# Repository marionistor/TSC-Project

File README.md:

# OpenBook

OpenBook este un e-book reader open-source, construit pentru consum mic de energie și versatilitate. Folosește microcontrollerul ESP32-C6-WROOM-1-N8, un ecran e-paper, senzori ambientali, ceas în timp real și stocare extinsă, alimentate de o baterie reîncărcabilă.

## Bill of Materials

| Componentă | Descriere | Link Achiziție | Documentație |
|------------|-----------|----------------|--------------|
| ESP32-C6-WROOM-1-N8 | Microcontroler cu Wi-Fi 6, BLE 5.0 | [Mouser](https://ro.mouser.com/ProductDetail/Espressif-Systems/ESP32-C6-WROOM-1-N8) | [Datasheet](https://www.espressif.com/sites/default/files/documentation/esp32-c6-wroom-1_wroom-1u_datasheet_en.pdf) |
| BME680 | Senzor temperatură, umiditate, presiune, VOC | [Mouser](https://ro.mouser.com/ProductDetail/Bosch-Sensortec/BME680) | [Datasheet](https://www.bosch-sensortec.com/media/boschsensortec/downloads/datasheets/bst-bme680-ds001.pdf) |
| DS3231SN | Ceas în timp real | [Mouser](https://ro.mouser.com/ProductDetail/Analog-Devices/DS3231SN) | [Datasheet](https://www.analog.com/media/en/technical-documentation/data-sheets/DS3231.pdf) |
| W25Q512JVEIQ | Memorie Flash 64MB | [Mouser](https://ro.mouser.com/ProductDetail/Winbond/W25Q512JVEIQ) | [Datasheet](https://www.winbond.com/resource-files/W25Q512JV%20SPI%20RevB%2006252019%20KMS.pdf) |
| MicroSD Slot (112A-TAAR-R03) | Slot card microSD | [Mouser](https://ro.mouser.com/ProductDetail/Attend/112A-TAAR-R03) | [Datasheet](https://www.attend.com.tw/data/download/file/112A-TAAR-R03_Spec.pdf) |
| MCP73831T-5ACI/OT | Încărcător baterie | [Mouser](https://ro.mouser.com/ProductDetail/Microchip-Technology/MCP73831T-5ACI-OT) | [Datasheet](https://ww1.microchip.com/downloads/en/DeviceDoc/MCP73831-Family-Data-Sheet-DS20001984H.pdf) |
| MAX17048G+T10 | Indicator nivel baterie | [Mouser](https://ro.mouser.com/ProductDetail/Analog-Devices/MAX17048G%2BT10) | [Datasheet](https://www.analog.com/media/en/technical-documentation/data-sheets/MAX17048-MAX17049.pdf) |
| XC6220A331MR-G | Regulator 3.3V | [Mouser](https://ro.mouser.com/ProductDetail/Torex-Semiconductor/XC6220A331MR-G) | [Datasheet](https://www.torexsemi.com/file/xc6220/XC6220.pdf) |
| USB4110-GF-A | Conector USB-C | [Mouser](https://ro.mouser.com/ProductDetail/GCT/USB4110-GF-A) | [Datasheet](https://gct.co/files/drawings/usb4110.pdf) |
| CPH3225A | Supercondensator pentru ceas | [Mouser](https://ro.mouser.com/ProductDetail/Seiko-Instruments/CPH3225A) | [Datasheet](https://mm.digikey.com/Volume0/opasdata/d220001/medias/docus/6537/rev05-CPHCPM.pdf) |
| DMG2305UX-7 | MOSFET P-Channel | [Mouser](https://ro.mouser.com/ProductDetail/Diodes-Incorporated/DMG2305UX-7) | [Datasheet](https://www.diodes.com/assets/Datasheets/DMG2305UX.pdf) |
| SI1308EDL-T1-GE3 | MOSFET N-Channel | [Mouser](https://ro.mouser.com/ProductDetail/Vishay-Siliconix/SI1308EDL-T1-GE3) | [Datasheet](https://www.vishay.com/docs/63399/si1308edl.pdf) |
| USBLC6-2SC6Y | Protecție ESD USB | [Mouser](https://ro.mouser.com/ProductDetail/STMicroelectronics/USBLC6-2SC6Y) | [Datasheet](https://www.st.com/resource/en/datasheet/usblc6-2.pdf) |
| PGB1010603MR | Protecție ESD | [Mouser](https://ro.mouser.com/ProductDetail/Littelfuse/PGB1010603MR) | [Datasheet](https://www.littelfuse.com/~/media/electronics/datasheets/esd_protection/littelfuse_pulseguard_esd_pgb1_series_datasheet.pdf) |
| BD5229G-TR | Detector tensiune | [Mouser](https://ro.mouser.com/ProductDetail/ROHM-Semiconductor/BD5229G-TR) | [Datasheet](https://fscdn.rohm.com/en/products/databook/datasheet/ic/power/voltage_detector/bd52xxg-e.pdf) |
| FH34SRJ-24S-0.5SH(99) | Conector FFC/FPC e-paper | [Mouser](https://ro.mouser.com/ProductDetail/Hirose-Connector/FH34SRJ-24S-0.5SH99) | [Datasheet](https://www.hirose.com/product/document?clcode=&productname=&series=FH34SRJ&documenttype=Catalog&lang=en) |
| 744043680 | Inductor | [Mouser](https://ro.mouser.com/ProductDetail/Wurth-Elektronik/744043680) | [Datasheet](https://www.we-online.com/components/products/datasheet/744043680.pdf) |
| EVQPUJ02K | Buton tactil | [Mouser](https://ro.mouser.com/ProductDetail/Panasonic/EVQPUJ02K) | [Datasheet](https://www.lcsc.com/datasheet/lcsc_datasheet_2201121800_PANASONIC-EVQPUJ02K_C2936858.pdf) |
| KP-1608SURCK | LED indicator | [Mouser](https://ro.mouser.com/ProductDetail/Kingbright/KP-1608SURCK) | [Datasheet](https://media.elv.com/file/107153_led_surck1608_data.pdf) |

## Funcționalitate Hardware

### 1. Microcontroler ESP32-C6-WROOM-1-N8
* Rol: Gestionează toate funcțiile, de la afișaj la conectivitate wireless
* Specificații: Procesor 32-bit, 160 MHz, 512 KB SRAM, Wi-Fi 6, Bluetooth 5.0
* Conexiuni:
  * SPI: Conectează ecranul, memoria Flash și cardul SD
  * I²C: Interfațează senzorul, ceasul și indicatorul de baterie
  * GPIO: Controlează butoanele și alte funcții
  * UART: Utilizat pentru depanare
* Consum: 3.3V, sub 10 µA în mod repaus

### 2. Ecran E-Paper
* Tip: 7.5 inci, rezoluție 800x480 pixeli
* Conexiune: SPI, cu linii pentru date, control și stare
* Consum: 20-50 mA la reîmprospătare, aproape zero în mod static
* Rol: Afișează text clar, ideal pentru lectură prelungită

### 3. Stocare
* Memorie Flash (W25Q512JVEIQ):
  * Capacitate: 64 MB, conectată prin SPI
  * Scop: Stochează firmware și cărți
  * Consum: 10-20 mA
* Slot MicroSD:
  * Conexiune: SPI, pentru stocare suplimentară
  * Consum: 30-100 mA la citire/scriere

### 4. Ceas în Timp Real (DS3231SN)
* Conexiune: I2C, partajat cu alte module
* Consum: Sub 1 µA cu supercondensator
* Rol: Menține ora exactă pentru loguri sau programări

### 5. Senzor Ambiental (BME680)
* Măsurători: Temperatură, umiditate, presiune, compuși volatili
* Conexiune: I2C, viteză de 400 kHz
* Consum: 0.8-3.6 mA în funcționare, sub 1 µA în repaus
* Rol: Monitorizează mediul pentru ajustări sau date

### 6. Alimentare
* Baterie: Li-Po, 2500 mAh, 3.7V
* Încărcare: MCP73831, maxim 1A prin USB-C
* Monitorizare: MAX17048, consum ~50 µA
* Regulator: 3.3V stabil
* Protecție: Împotriva descărcărilor electrostatice și polarității greșite

### 7. Interfață Utilizator
* Butoane: Trei tactile pentru navigare
* LED: Indică starea dispozitivului

### 8. Extensii
* Conector Qwiic: Pentru senzori I2C suplimentari
* Pini GPIO: Pentru conectarea altor module

## Pini ESP32-C6

| Pin    | Semnal       | Funcție                          | Motiv                                  |
|--------|--------------|----------------------------------|----------------------------------------|
| EN     | RESET        | Resetare sistem                  | Pin standard pentru resetare           |
| IO0    | INT_RTC      | Întrerupere RTC                  | Capacitate de întrerupere low-power    |
| IO1    | 32KHZ        | Ieșire ceas RTC 32 kHz           | Asigură cronometrare precisă           |
| IO2    | MISO         | Intrare date SPI                 | Comun pentru magistrala SPI            |
| IO3    | EPD_BUSY     | Stare ocupat e-paper             | Verifică disponibilitatea afișajului   |
| IO4    | SS_SD        | Selectare card SD                | CS dedicat pentru card SD              |
| IO5    | EPD_DC       | Date/comenzi e-paper             | Distinge datele de comenzi             |
| IO6    | SCK          | Ceas SPI                         | Semnal comun de ceas pentru SPI        |
| IO7    | MOSI         | Ieșire date SPI                  | Comun pentru periferice SPI            |
| IO9    | IO/BOOT      | Buton pornire                    | Inițiază modul boot sau pornire        |
| IO10   | EPD_CS       | Selectare e-paper                | CS dedicat pentru afișaj               |
| IO11   | FLASH_CS     | Selectare Flash                  | CS dedicat pentru memoria Flash        |
| IO12   | USB_D-       | Date diferențiale USB -          | Pin fix pentru USB                     |
| IO13   | USB_D+       | Date diferențiale USB +          | Pin fix pentru USB                     |
| IO15   | IO/CHANGE    | Buton schimbare pagină           | Intrare utilizator pentru navigare     |
| IO18   | RTC_RST      | Resetare RTC                     | Resetare hardware pentru ceas          |
| IO21   | SDA          | Linie date I²C                   | Comun pentru senzori și RTC            |
| IO22   | SCL          | Linie ceas I²C                   | Semnal comun de ceas I²C               |
| IO23   | EPD_RST      | Resetare e-paper                 | Resetare hardware pentru afișaj        |
| TXD0   | TX           | Transmitere UART (depanare)      | Punct test pentru depanare             |
| RXD0   | RX           | Recepție UART (depanare)         | Punct test pentru depanare             |

## Decizii de Proiectare

* Alimentare stabilă: Liniile de putere au fost trasate cu prioritate pentru a garanta o funcționare fiabilă, restul semnalelor fiind optimizate automat.
* Conector USB-C: Configurat special pentru a elimina conflictele de design, permițând atât alimentare, cât și transfer de date.
* Afișaj e-paper: Ales pentru consum energetic minim și claritate, alimentat printr-un circuit dedicat cu tranzistor pentru eficiență.
* Extensibilitate: Include un port Qwiic și pini accesibili pentru viitoare modificări sau depanare ușoară.
* Protecție electrică: Adăugate circuite de siguranță pentru liniile de date și alimentare, asigurând rezistența dispozitivului.

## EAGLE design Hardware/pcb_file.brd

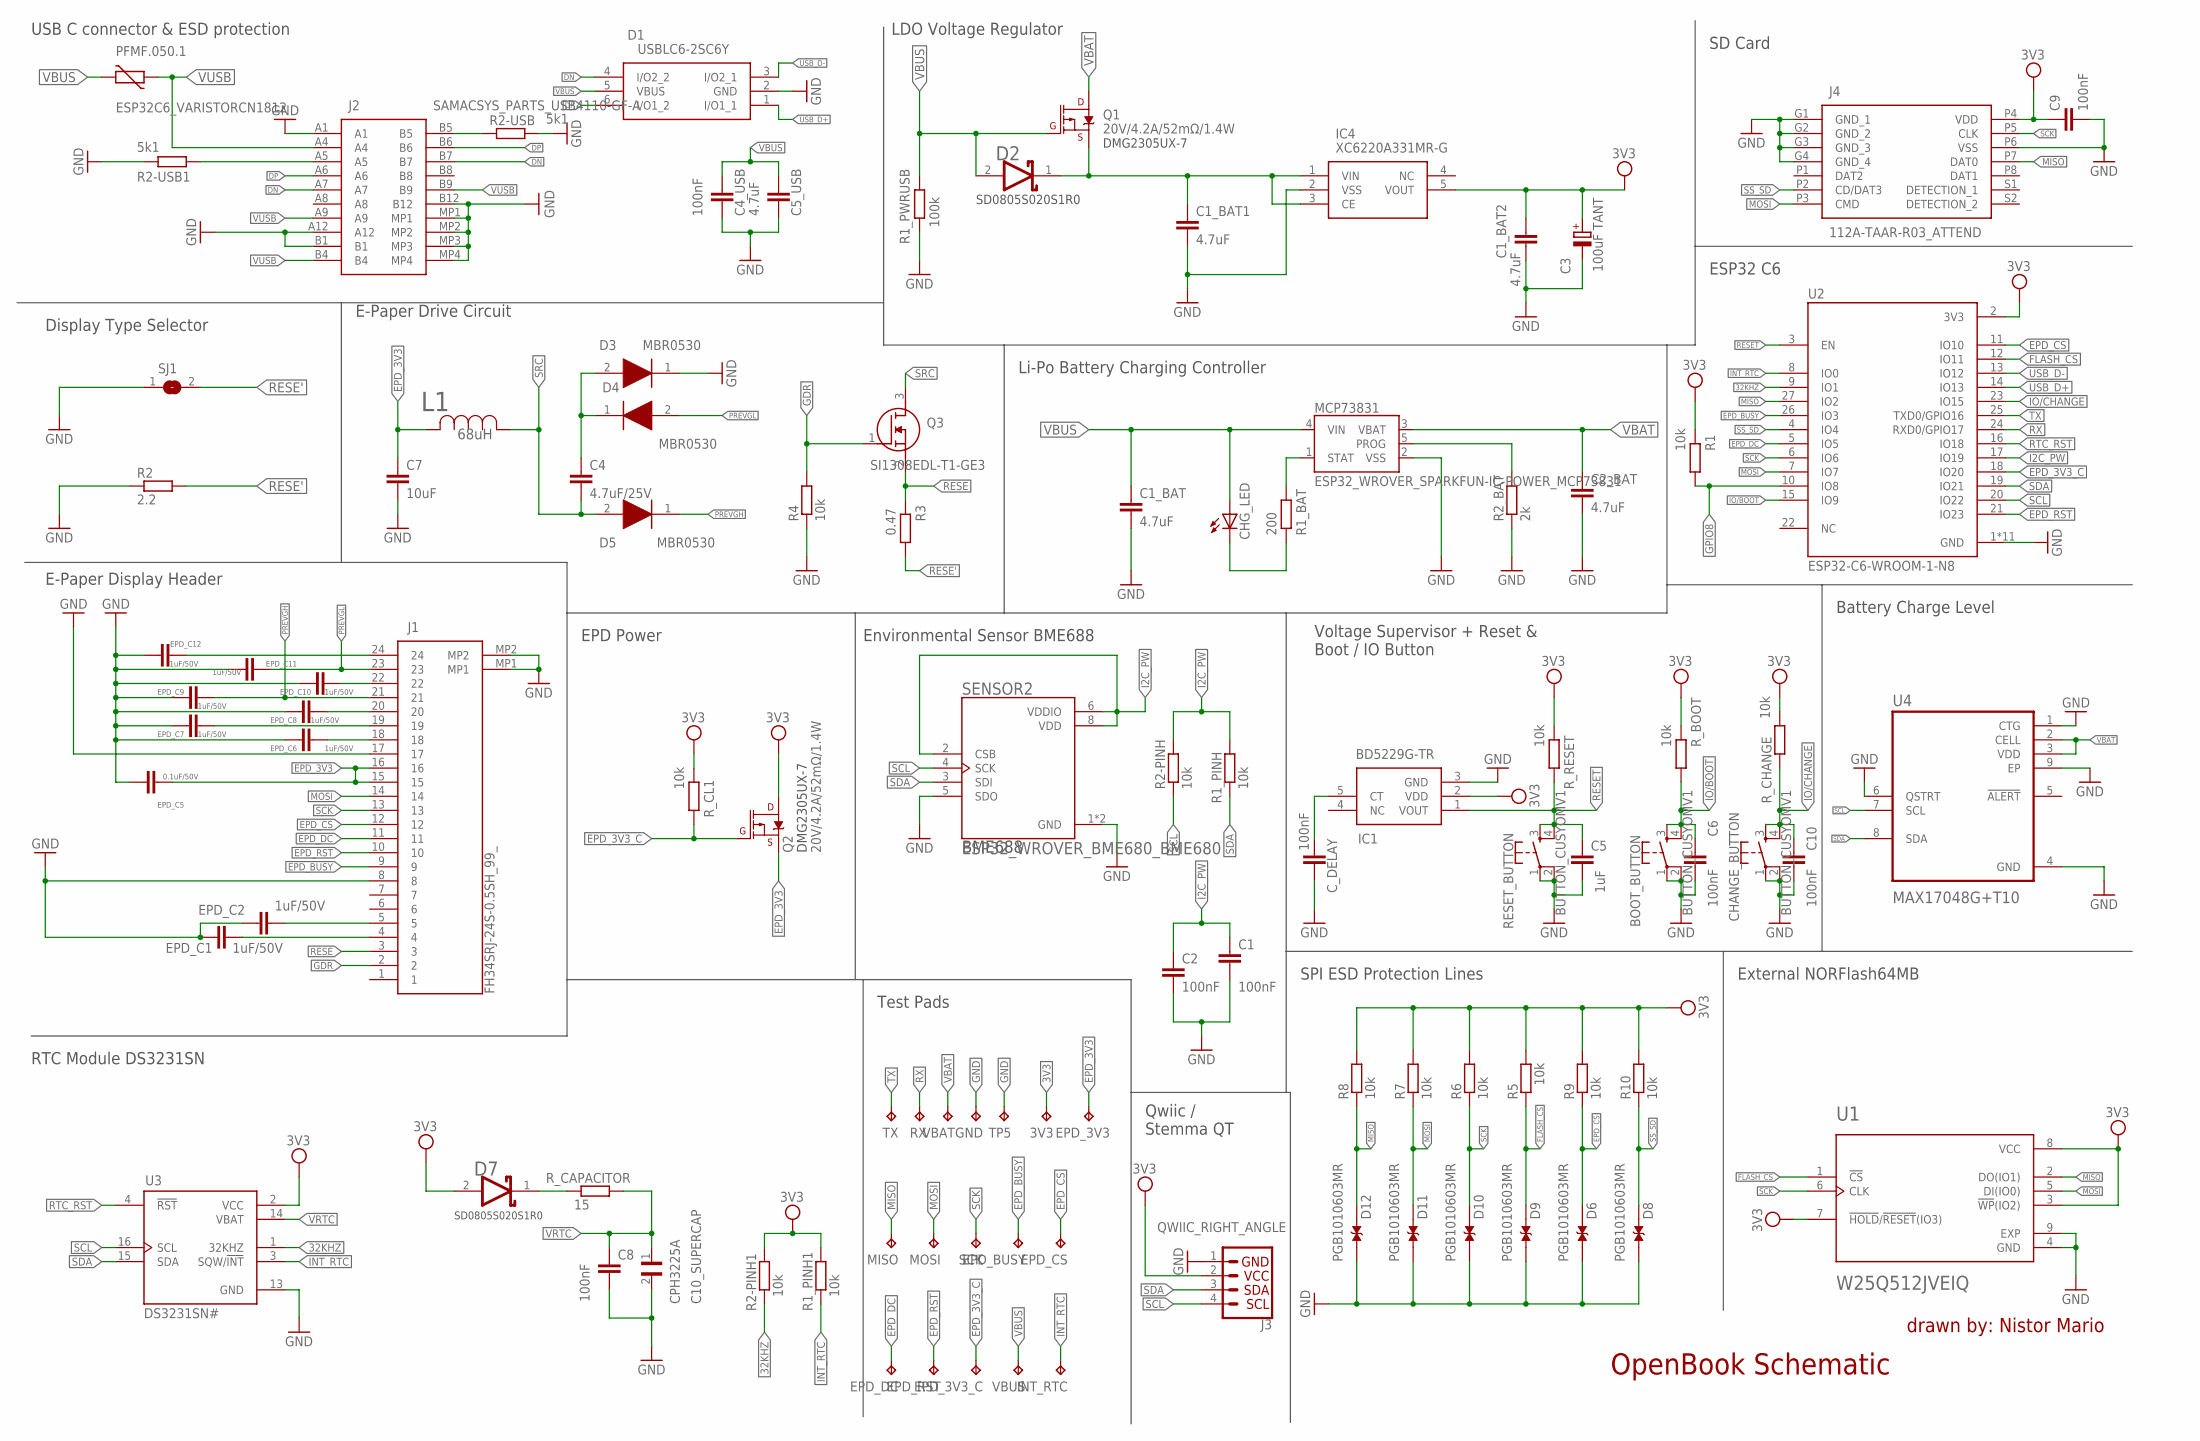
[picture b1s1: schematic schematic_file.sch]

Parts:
3V3: TPTP20R; TP20R
BOOT_BUTTON: BUTTON_CUSYOMV1; MYBUTTON
C1, C2, C8, C9: 100nF; EAGLE-LTSPICE_C0402
C1_BAT, C1_BAT2, C5_USB: 4.7uF; ESP32_WROVER_EAGLE-LTSPICE_C0402
C1_BAT1, C2_BAT: 4.7uF; EAGLE-LTSPICE_C0402
C3: 100uF TANT; RCL_CT3528
C4: 4.7uF/25V; EAGLE-LTSPICE_C0402
C4_USB, C6, C10: 100nF; ESP32_WROVER_EAGLE-LTSPICE_C0402
C5: 1uF; EAGLE-LTSPICE_C0402
C7: 10uF; EAGLE-LTSPICE_C0402
C10_SUPERCAP: CPH3225A; CAPCP3225X100N
CHANGE_BUTTON: BUTTON_CUSYOMV1; MYBUTTON
CHG_LED: ADAFRUIT_LEDCHIP-LED0603; ADAFRUIT_CHIP-LED0603
C_DELAY: 100nF; EAGLE-LTSPICE_C0402
D1: USBLC6-2SC6Y; SOT95P280X145-6N
D2, D7: ESP32_WROVER_AVX---SD0805S020S1R0_AVX_SD0805S020S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; ESP32_WROVER_AVX---SD0805S020S1R0_AVX_SD0805S020S1R0_0
D3, D4, D5: MBR0530; SOD3716X135N
D6, D8, D9, D10, D11, D12: PGB1010603MR; DIOC1608X36N
EPD_3V3, EPD_3V3_C: TPTP20R; TP20R
EPD_BUSY: TPTP20R; TP20R
EPD_C1, EPD_C2, EPD_C6, EPD_C7, EPD_C8, EPD_C9, EPD_C10, EPD_C11, EPD_C12: 1uF/50V; ESP32_WROVER_EAGLE-LTSPICE_C0402
EPD_C5: 0.1uF/50V; ESP32_WROVER_EAGLE-LTSPICE_C0402
EPD_CS: TPTP20R; TP20R
EPD_DC: TPTP20R; TP20R
EPD_RST: TPTP20R; TP20R
GND: TPTP20R; TP20R
IC1: BD5229G-TR; SOT95P280X125-5N
IC4: XC6220A331MR-G; SOT95P280X120-5N
INT_RTC: TPTP20R; TP20R
J1: FH34SRJ-24S-0.5SH_99_; FH34SRJ24S05SH99
J2: SAMACSYS_PARTS_USB4110-GF-A; SAMACSYS_PARTS_USB4110GFA
J3: QWIIC_RIGHT_ANGLE; JST04_1MM_RA
J4: 112A-TAAR-R03_ATTEND; 112ATAARR03ATTEND
L1: 68uH; IND_4828-WE-TPC_WRE
MCP73831: ESP32_WROVER_SPARKFUN-IC-POWER_MCP73831; ESP32_WROVER_SPARKFUN-IC-POWER_SOT23-5
MISO: TPTP20R; TP20R
MOSI: TPTP20R; TP20R
PFMF.050.1: ESP32C6_VARISTORCN1812; ESP32C6_VARISTOR_CT/CN1812
Q1, Q2: 20V/4.2A/52mΩ/1.4W; ESP32_WROVER_SPARKFUN-DISCRETESEMI_SOT23-3
Q3: SI1308EDL-T1-GE3; SOT65P210X110-3N
R1, R1_PINH, R1_PINH1, R2-PINH, R2-PINH1, R4, R5, R6, R7, R8, R9, R10: 10k; ESP32_WROVER_EAGLE-LTSPICE_R0402
R1_BAT: 200; ESP32_WROVER_EAGLE-LTSPICE_R0402
R1_PWRUSB: 100k; ESP32_WROVER_EAGLE-LTSPICE_R0402
R2: 2.2; ESP32_WROVER_EAGLE-LTSPICE_R0402
R2-USB, R2-USB1: 5k1; ESP32_WROVER_EAGLE-LTSPICE_R0402
R2_BAT: 2k; ESP32_WROVER_EAGLE-LTSPICE_R0402
R3: 0.47; ESP32_WROVER_EAGLE-LTSPICE_R0402
RESET_BUTTON: BUTTON_CUSYOMV1; MYBUTTON
RX: TPTP20R; TP20R
R_BOOT: 10k; ESP32_WROVER_EAGLE-LTSPICE_R0402
R_CAPACITOR: 15; ESP32_WROVER_EAGLE-LTSPICE_R0402
R_CHANGE: 10k; ESP32_WROVER_EAGLE-LTSPICE_R0402
R_CL1: 10k; ESP32_WROVER_EAGLE-LTSPICE_R0402
R_RESET: 10k; ESP32_WROVER_EAGLE-LTSPICE_R0402
SCK: TPTP20R; TP20R
SENSOR2: ESP32_WROVER_BME680_BME680; ESP32_WROVER_BME680_PSON80P300X300X100-8N
SJ1: SJ
TP5: TPTP20R; TP20R
TX: TPTP20R; TP20R
U1: W25Q512JVEIQ; SON127P600X800X80-9N
U2: ESP32-C6-WROOM-1-N8; XCVR_ESP32-C6-WROOM-1-N8
U3: DS3231SN#; SOIC127P1032X265-16N
U4: MAX17048G+T10; SON50P200X200X80-9N
VBAT: TPTP20R; TP20R
VBUS: TPTP20R; TP20R

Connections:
3V3: 3V3.TP, C1_BAT2.1, C3.+, C9.1, D7.2 (ANODE), IC1.2 (VDD), IC4.5 (VOUT), J3.2, J4.P4 (VDD), Q2.3 (D), R1.2, R1_PINH1.2, R2-PINH1.2, R5.2, R6.2, R7.2, R8.2, R9.2, R10.2, R_BOOT.2, R_CHANGE.2, R_CL1.2, R_RESET.2, U1.3 (!WP!(IO2)), U1.7 (!HOLD!/!RESET!(IO3)), U1.8 (VCC), U2.2 (3V3), U3.2 (VCC)
32KHZ: R2-PINH1.1, U2.9 (IO1), U3.1 (32KHZ)
DN: D1.4 (I/O2_2), J2.A7, J2.B7
DP: D1.6 (I/O1_2), J2.A6, J2.B6
EPD_3V3: C7.1, EPD_3V3.TP, EPD_C5.2, J1.15, J1.16, L1.2, Q2.2 (S)
EPD_3V3_C: EPD_3V3_C.TP, Q2.1 (G), R_CL1.1, U2.18 (IO20)
EPD_BUSY: EPD_BUSY.TP, J1.9, U2.26 (IO3)
EPD_CS: D6.2, EPD_CS.TP, J1.12, R9.1, U2.11 (IO10)
EPD_DC: EPD_DC.TP, J1.11, U2.5 (IO5)
EPD_RST: EPD_RST.TP, J1.10, U2.21 (IO23)
FLASH_CS: D9.2, R5.1, U1.1 (!CS), U2.12 (IO11)
GDR: J1.2, Q3.1 (G), R4.2
GND: BOOT_BUTTON.1, BOOT_BUTTON.2, C1.2, C1_BAT.2, C1_BAT1.2, C1_BAT2.2, C2.2, C2_BAT.2, C3.-, C4_USB.2, C5.2, C5_USB.2, C6.2, C7.2, C8.2, C9.2, C10.2, C10_SUPERCAP.2, CHANGE_BUTTON.1, CHANGE_BUTTON.2, C_DELAY.2, D1.2 (GND), D3.1 (K), D6.1, D8.1, D9.1, D10.1, D11.1, D12.1, EPD_C1.1, EPD_C2.1, EPD_C5.1, EPD_C6.1, EPD_C7.1, EPD_C8.1, EPD_C9.1, EPD_C10.1, EPD_C11.1, EPD_C12.1, GND.TP, IC1.3 (GND), IC4.2 (VSS), J1.8, J1.17, J1.MP1, J1.MP2, J2.A1, J2.A12, J2.B1, J2.B12, J2.MP1, J2.MP2, J2.MP3, J2.MP4, J3.1, J4.G1 (GND_1), J4.G2 (GND_2), J4.G3 (GND_3), J4.G4 (GND_4), J4.P6 (VSS), MCP73831.2 (VSS), R1_PWRUSB.2, R2.1, R2-USB.2, R2-USB1.1, R2_BAT.1, R4.1, RESET_BUTTON.1, RESET_BUTTON.2, SENSOR2.1 (GND), SENSOR2.5 (SDO), SENSOR2.7 (GND), SJ1.1, TP5.TP, U1.4 (GND), U1.9 (EXP), U2.1 (GND), U2.28 (GND), U2.29_1 (GND), U2.29_2 (GND), U2.29_3 (GND), U2.29_4 (GND), U2.29_5 (GND), U2.29_6 (GND), U2.29_7 (GND), U2.29_8 (GND), U2.29_9 (GND), U3.13 (GND), U4.1 (CTG), U4.4 (GND), U4.6 (QSTRT), U4.9 (EP); also elsewhere on the board
GPIO8: R1.1, U2.10 (IO8)
I2C_PW: C1.1, C2.1, R1_PINH.2, R2-PINH.2, SENSOR2.2 (CSB), SENSOR2.6 (VDDIO), SENSOR2.8 (VDD), U2.17 (IO19)
INT_RTC: INT_RTC.TP, R1_PINH1.1, U2.8 (IO0), U3.3 (SQW/!INT)
IO/BOOT: BOOT_BUTTON.3, BOOT_BUTTON.4, C6.1, R_BOOT.1, U2.15 (IO9)
IO/CHANGE: C10.1, CHANGE_BUTTON.3, CHANGE_BUTTON.4, R_CHANGE.1, U2.23 (IO15)
MISO: D12.2, J4.P7 (DAT0), MISO.TP, R8.1, U1.2 (DO(IO1)), U2.27 (IO2)
MOSI: D11.2, J1.14, J4.P3 (CMD), MOSI.TP, R7.1, U1.5 (DI(IO0)), U2.7 (IO7)
unnamed: J2.A5, R2-USB1.2
unnamed: J2.B5, R2-USB.1
unnamed: EPD_C1.2, J1.4
unnamed: C1_BAT1.1, D2.1 (CATHODE), IC4.1 (VIN), IC4.3 (CE), Q1.2 (S)
unnamed: EPD_C2.2, J1.5
unnamed: EPD_C12.2, J1.24
unnamed: MCP73831.1 (STAT), R1_BAT.2
unnamed: C4.1, D3.2 (A), D4.1 (K)
unnamed: EPD_C10.2, J1.22
unnamed: CHG_LED.C, R1_BAT.1
unnamed: MCP73831.5 (PROG), R2_BAT.2
unnamed: EPD_C8.2, J1.20
unnamed: EPD_C7.2, J1.19
unnamed: EPD_C6.2, J1.18
unnamed: C_DELAY.1, IC1.5 (CT)
unnamed: D7.1 (CATHODE), R_CAPACITOR.1
PREVGH: D5.1 (K), EPD_C9.2, J1.21
PREVGL: D4.2 (A), EPD_C11.2, J1.23
RESE: J1.3, Q3.2 (S), R3.2
RESE': R2.2, R3.1, SJ1.2
RESET: C5.1, IC1.1 (VOUT), RESET_BUTTON.3, RESET_BUTTON.4, R_RESET.1, U2.3 (EN)
RTC_RST: U2.16 (IO18), U3.4 (!RST)
RX: RX.TP, U2.24 (RXD0/GPIO17)
SCK: D10.2, J1.13, J4.P5 (CLK), R6.1, SCK.TP, U1.6 (CLK), U2.6 (IO6)
SCL: J3.4, R2-PINH.1, SENSOR2.4 (SCK), U2.20 (IO22), U3.16 (SCL), U4.7 (SCL)
SDA: J3.3, R1_PINH.1, SENSOR2.3 (SDI), U2.19 (IO21), U3.15 (SDA), U4.8 (SDA)
SRC: C4.2, D5.2 (A), L1.1, Q3.3 (D)
SS_SD: D8.2, J4.P2 (CD/DAT3), R10.1, U2.4 (IO4)
TX: TX.TP, U2.25 (TXD0/GPIO16)
USB_D+: D1.1 (I/O1_1), U2.14 (IO13)
USB_D-: D1.3 (I/O2_1), U2.13 (IO12)
VBAT: C2_BAT.1, MCP73831.3 (VBAT), Q1.3 (D), U4.2 (CELL), U4.3 (VDD), VBAT.TP
VBUS: C1_BAT.1, C4_USB.1, C5_USB.1, CHG_LED.A, D1.5 (VBUS), D2.2 (ANODE), MCP73831.4 (VIN), PFMF.050.1.2, Q1.1 (G), R1_PWRUSB.1, VBUS.TP
VRTC: C8.1, C10_SUPERCAP.1, R_CAPACITOR.2, U3.14 (VBAT)
VUSB: J2.A4, J2.A9, J2.B4, J2.B9, PFMF.050.1.1

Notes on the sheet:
USB C connector & ESD protection
LDO Voltage Regulator
SD0805S020S1R0
DMG2305UX-7
SD Card
Display Type Selector
E-Paper Display Header
E-Paper Drive Circuit
Li-Po Battery Charging Controller
ESP32 C6
EPD Power
BME688
Environmental Sensor BME688
Voltage Supervisor + Reset & Boot / IO Button
Battery Charge Level
RTC Module DS3231SN
Test Pads
Qwiic / Stemma QT
External NORFlash64MB
SPI ESD Protection Lines
OpenBook Schematic
drawn by: Nistor Mario

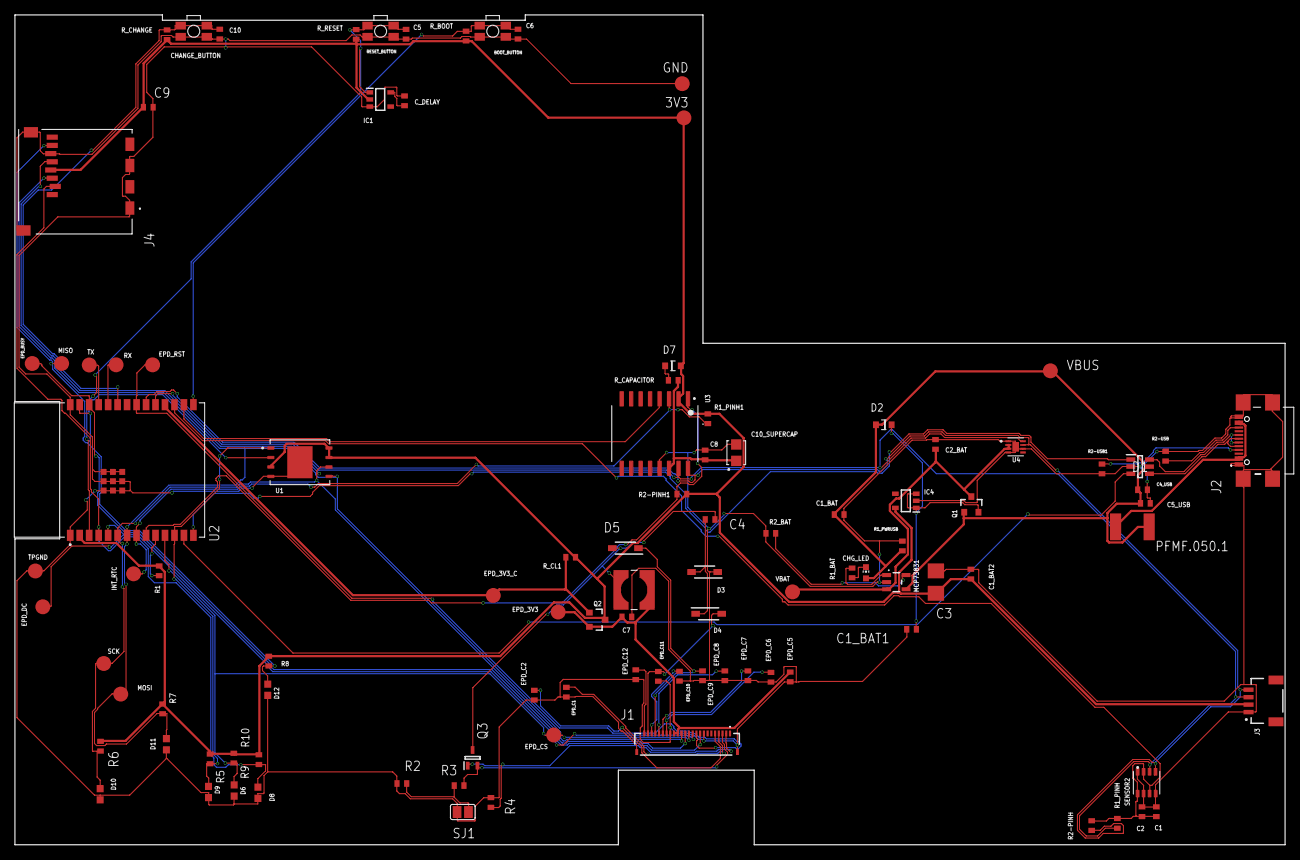
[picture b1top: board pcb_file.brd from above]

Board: 2 copper layers, 170.2 x 111.2 mm, 103 parts (0 on the bottom side), 55 nets.

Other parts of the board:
TPGND: TPTP20R; TP20R

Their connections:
GND: TPGND.TP; also elsewhere on the board

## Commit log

2025-04-06 Added project files
2025-04-06 Added license
2025-04-11 Fixed issues

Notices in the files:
parts and their libraries:
COPYRIGHT: Copyright (C) 2024 Ultra Librarian. All rights reserved.
